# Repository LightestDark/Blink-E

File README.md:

# Blink-E
I made a Blinker project in the shape of Wall-E as part of the Blueprint Program

# Schematic

# PCB

# 3D View

# CASE ASSEMBLY

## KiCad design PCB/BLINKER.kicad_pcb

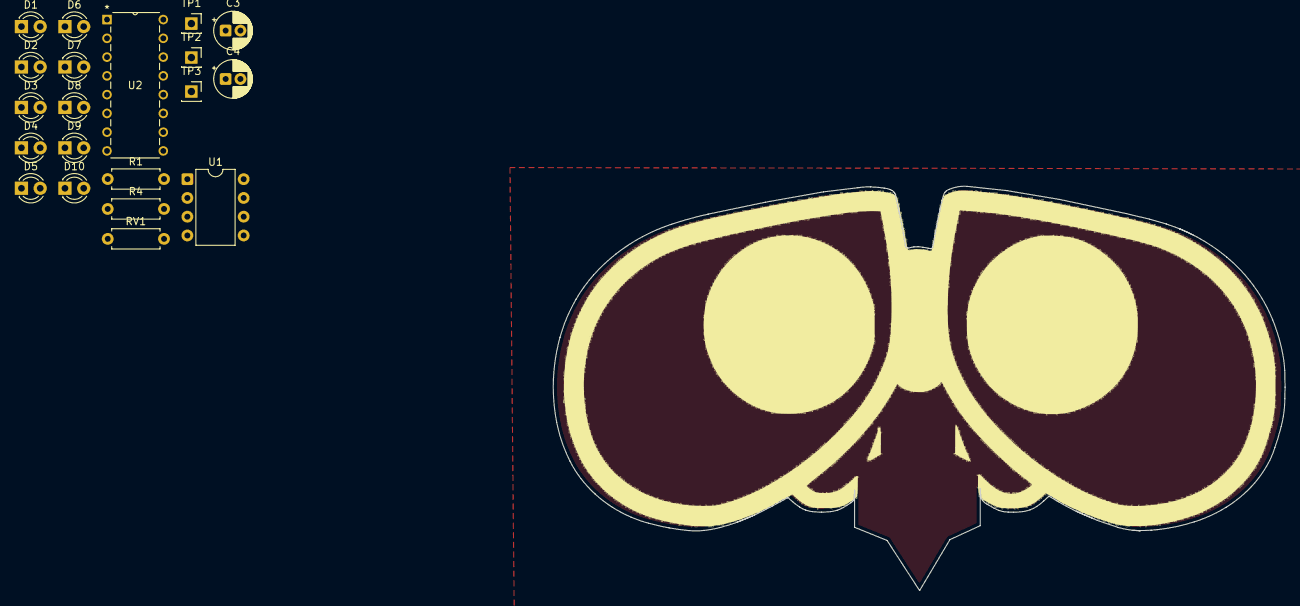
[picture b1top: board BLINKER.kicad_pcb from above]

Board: 2 copper layers, 99.0 x 54.7 mm, 20 parts (0 on the bottom side), 6 nets, no tracks yet.

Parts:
C3: 1 uF; CP_Radial_D5.0mm_P2.00mm
C4: 0.01 uF; CP_Radial_D5.0mm_P2.00mm
D1, D2, D3, D4, D5, D6, D7, D8, D9, D10: LED; LED_D3.0mm
R1: 1k; R_Axial_DIN0207_L6.3mm_D2.5mm_P7.62mm_Horizontal
R4: 470; R_Axial_DIN0207_L6.3mm_D2.5mm_P7.62mm_Horizontal
RV1: 50k; R_Axial_DIN0207_L6.3mm_D2.5mm_P7.62mm_Horizontal
TP1, TP2, TP3: TestPoint; PinSocket_1x01_P2.54mm_Vertical
U1: NE555P; DIP-8_W7.62mm
U2: 4017; N16

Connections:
+5V: TP1.1, U1.4 (R), U1.8 (VCC), U2.16 (VDD)
GND: C4.1, R4.2, TP2.1, U1.1 (GND), U2.8 (VSS), U2.13 (CKEN), U2.15 (Reset)
unnamed: D2.1 (K), D3.1 (K), D4.1 (K), D5.1 (K), D6.1 (K), D7.1 (K), D8.1 (K), D9.1 (K), D10.1 (K), R4.1
unnamed: RV1.1, RV1.2, U1.7 (DIS)
OUT: U1.3 (Q), U2.14 (CLK)
TR: U1.2 (TR), U1.6 (THR)

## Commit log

2026-01-05 Create a
